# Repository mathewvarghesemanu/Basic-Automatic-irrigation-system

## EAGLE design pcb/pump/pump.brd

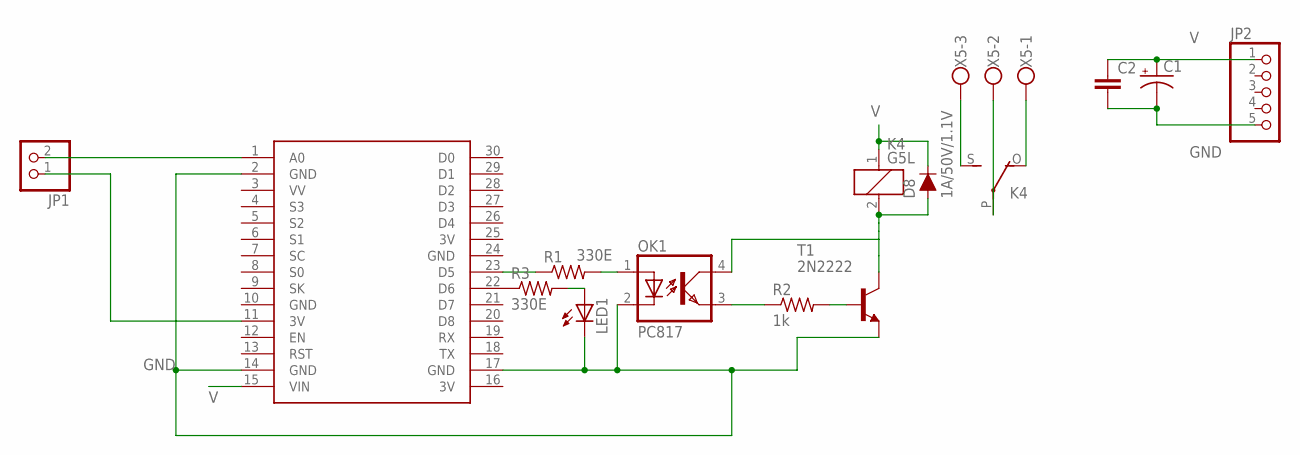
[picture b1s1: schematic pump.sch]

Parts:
C1: CPOL-USE5-5; E5-5
C2: C5/3; C5B3
D8: 1A/50V/1.1V; DIODE-1N4001
JP1: PINHD-1X2; 1X02
JP2: PINHD-1X5; 1X05
K4: G5L; G5LE
LED1: LED5MM
OK1: PC817; DIL04
R1, R3: 330E; 0204/7
R2: 1k; 0207/7
T1: 2N2222; TO92-EBC-OVAL
U$1: NODEMCU
X5: W237-103

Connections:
3V: U$1.16 (3V), U$1.25 (3V)
GND: C1.-, C2.2, JP2.5, LED1.K (C), OK1.2 (C), T1.E, U$1.2 (GND), U$1.10 (GND), U$1.14 (GND), U$1.17 (GND), U$1.24 (GND)
unnamed: R1.1, U$1.23 (D5)
unnamed: OK1.1 (A), R1.2
unnamed: OK1.3 (EMIT), R2.1
unnamed: R2.2, T1.B
unnamed: LED1.A, R3.2
unnamed: JP1.2, U$1.1 (A0)
unnamed: JP1.1, U$1.11 (3V)
unnamed: R3.1, U$1.22 (D6)
unnamed: K4.S, X5.3
unnamed: K4.O, X5.1
unnamed: K4.P, X5.2
unnamed: D8.A, K4.2, OK1.4 (COL), T1.C
V: C1.+, C2.1, D8.C, JP2.1, K4.1, U$1.15 (VIN)

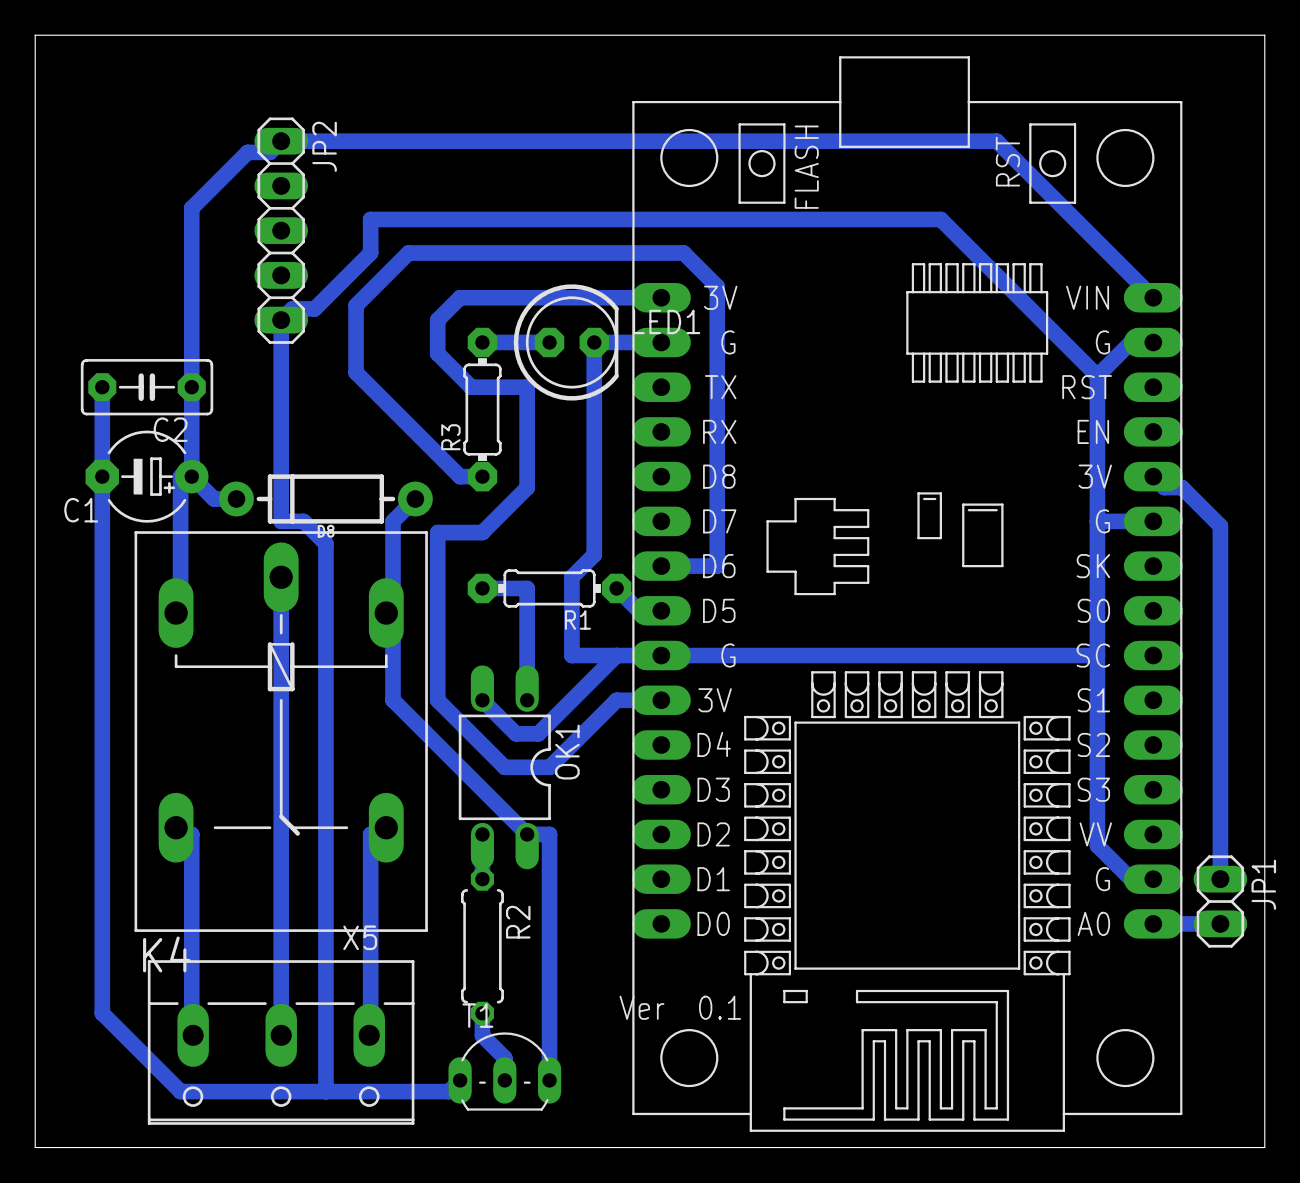
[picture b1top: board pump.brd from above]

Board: 2 copper layers, 69.8 x 63.2 mm, 14 parts (0 on the bottom side), 15 nets.

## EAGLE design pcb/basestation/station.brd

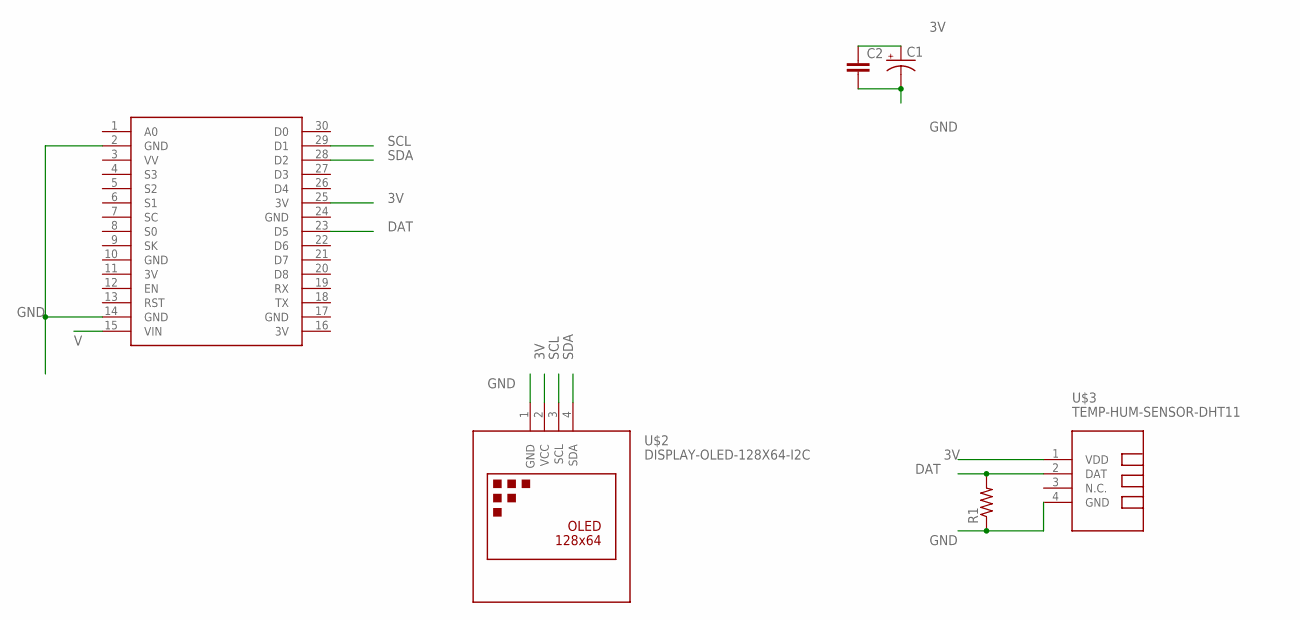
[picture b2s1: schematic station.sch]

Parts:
C1: CPOL-USE5-5; E5-5
C2: C5/3; C5B3
R1: R-US_0207/7; 0207/7
U$1: NODEMCU
U$2: DISPLAY-OLED-128X64-I2C
U$3: TEMP-HUM-SENSOR-DHT11

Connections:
3V: C1.+, C2.1, U$1.11 (3V), U$1.16 (3V), U$1.25 (3V), U$2.2 (VCC), U$3.1 (VDD)
DAT: R1.2, U$1.23 (D5), U$3.2 (DAT)
GND: C1.-, C2.2, R1.1, U$1.2 (GND), U$1.10 (GND), U$1.14 (GND), U$1.17 (GND), U$1.24 (GND), U$2.1 (GND), U$3.4 (GND)
SCL: U$1.29 (D1), U$2.3 (SCL)
SDA: U$1.28 (D2), U$2.4 (SDA)
V: U$1.15 (VIN)

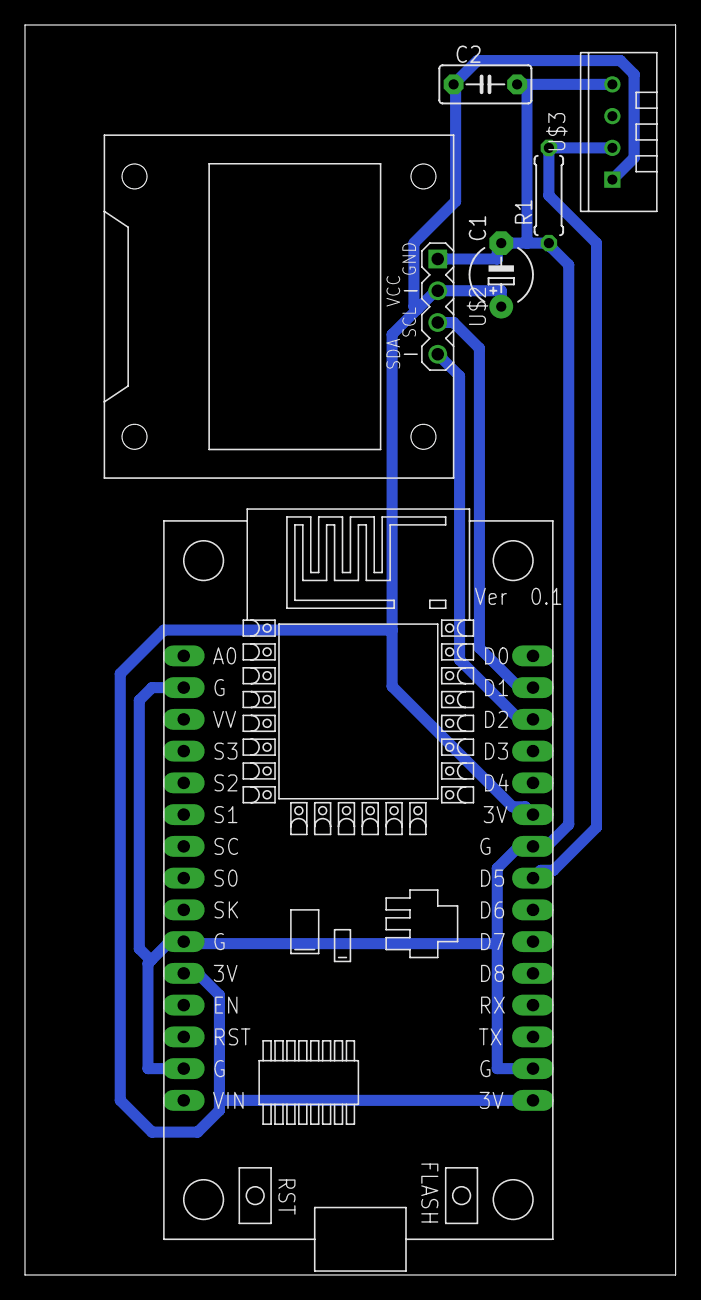
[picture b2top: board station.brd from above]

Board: 2 copper layers, 52.0 x 100.0 mm, 6 parts (0 on the bottom side), 5 nets.

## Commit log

2019-02-23 v1
    initial commit
2019-02-23 v2
    Basic communicated with thingermoisture node
2019-02-24 v2
    Dht11 node completed
2019-02-24 v3
    moisturenode completed
2019-02-25 final update
2019-03-19 pcb added
2019-09-17 final version

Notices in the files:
parts and their libraries:
diy-modules: Released under the Creative Commons Attribution 4.0 International License: http://creativecommons.org/licenses/by/4.0
SparkFun-DiscreteSemi: Licensing: Creative Commons ShareAlike 4.0 International - https://creativecommons.org/licenses/by-sa/4.0
